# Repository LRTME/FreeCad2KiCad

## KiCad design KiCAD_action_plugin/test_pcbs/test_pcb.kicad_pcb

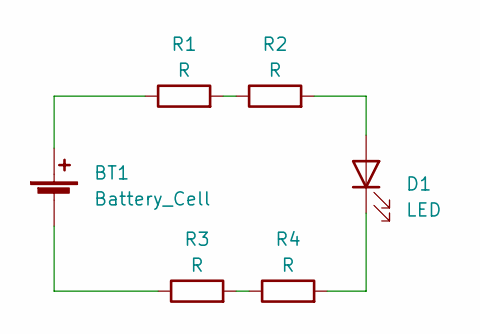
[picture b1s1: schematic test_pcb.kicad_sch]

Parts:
BT1: Battery_Cell; PinHeader_1x02_P1.00mm_Vertical
D1: LED; LED_D5.0mm
R1, R2: R; R_Axial_DIN0204_L3.6mm_D1.6mm_P5.08mm_Horizontal
R3, R4: R; R_1812_4532Metric_Pad1.30x3.40mm_HandSolder

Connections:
unnamed: BT1.1 (+), R1.1
unnamed: BT1.2 (-), R3.1
unnamed: D1.2 (A), R2.2
unnamed: D1.1 (K), R4.2
unnamed: R1.2, R2.1
unnamed: R3.2, R4.1

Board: 2 copper layers, 6 parts (2 on the bottom side), 6 nets, no tracks yet.

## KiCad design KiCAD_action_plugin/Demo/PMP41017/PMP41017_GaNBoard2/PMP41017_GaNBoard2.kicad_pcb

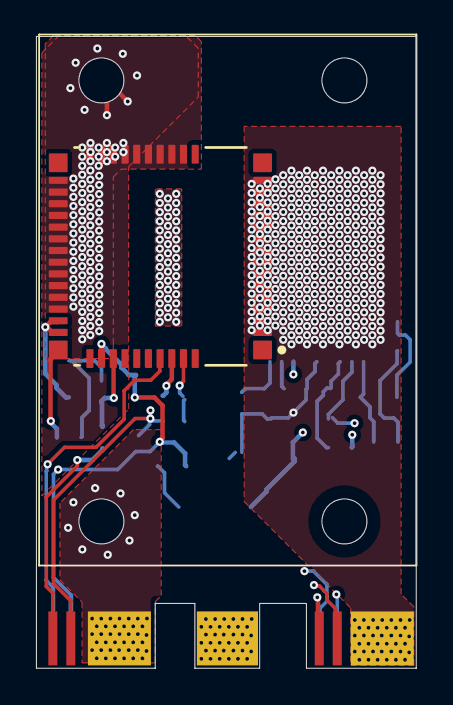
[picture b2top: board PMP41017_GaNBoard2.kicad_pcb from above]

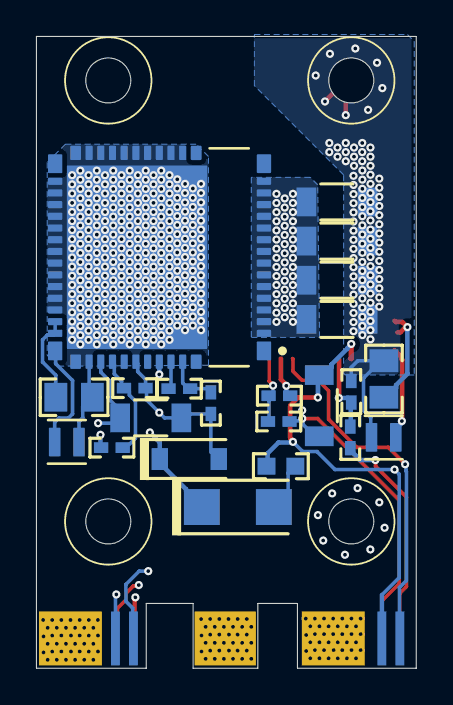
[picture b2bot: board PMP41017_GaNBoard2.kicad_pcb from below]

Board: 4 copper layers, 21.1 x 35.1 mm, 28 parts (27 on the bottom side), 20 nets.

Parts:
C156, C161: C1206C106K3RACTU; 1206_190
C157, C162: CL05B224KO5NNNC; 0402
C158, C163: GRM219R61E225KA12D; 0805_HV
C160, C173: C1005C0G1H220J050BA; 0402
C164, C165, C166, C167: C1206C223KDRACTU; 1206_190
D7: US1M-13-F; SMA
D8: BZT52C16-7-F; SOD-123
J9: Edge Finger; EC_GAN_DC_HBLLC
L7, L8: SDEM20161T-4R7MS; FP-SDEM20161T-4R7MS_SMD2-MFG
R103: MCT06030C2008FP500; 0603
R104, R107: MCR01MZPJ000; 0402
R106, R109: CRCW0402300RJNED; 0402
TH5, TH6, TH7, TH8: M2.5 SCREW; TP_H045P075
U18: LMG3425R030RQZT; RQZ0054A-MFG-NV
U19: LMG3522R030Q; RQS0052A-MFG

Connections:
5V_H: C157.1, R104.2, U18.53
5V_L: C162.2, R107.2, U19.51
HVBUS: C164.1, C165.1, C166.1, C167.1, J9.HV, U18.2, U18.3, U18.4, U18.5, U18.6, U18.7, U18.8, U18.9, U18.10, U18.11, U18.12, U18.13, U18.14, U18.15
INH: J9.6, R106.1
INL: J9.2, R109.1
ISO_12V_H: C156.1, D7.1, D8.1, J9.7, U18.46
ISO_12V_L: C161.2, J9.3, R103.2, U19.44
NetC160_2: C160.2, R106.2, U18.47
NetC173_2: C173.2, R109.2, U19.45
NetD7_2: D7.2, R103.1
NetL7_2: L7.2, U18.43
NetL8_2: L8.2, U19.42
NetR107_1: R107.1, U19.50
PGND: C161.1, C162.1, C163.2, C164.2, C165.2, C166.2, C167.2, C173.1, J9.4, J9.PG, L8.1, U19.18, U19.19, U19.20, U19.21, U19.22, U19.23, U19.24, U19.25, U19.26, U19.28, U19.29, U19.30, U19.31, U19.32, U19.33, U19.34, U19.35, U19.36, U19.37, U19.38, U19.39
RDRV_H_1: R104.1, U18.52
SW: C156.2, C157.2, C158.2, C160.1, D8.2, J9.8, J9.SW, L7.1, U18.18, U18.19, U18.20, U18.21, U18.22, U18.23, U18.24, U18.25, U18.26, U18.27, U18.29, U18.30, U18.31, U18.32, U18.33, U18.34, U18.35, U18.36, U18.37, U18.38, U18.39, U18.40, U18.44, U18.45, U18.49, U18.55, U19.2, U19.3, U19.4, U19.5, U19.6, U19.7, U19.8, U19.9, U19.10, U19.11, U19.12, U19.13, U19.14, U19.15
TEMP_H_1: J9.5, U18.51
TEMP_L_1: J9.1, U19.49
VNEG_H_1: C158.1, U18.41, U18.42
VNEG_L_1: C163.1, U19.40, U19.41

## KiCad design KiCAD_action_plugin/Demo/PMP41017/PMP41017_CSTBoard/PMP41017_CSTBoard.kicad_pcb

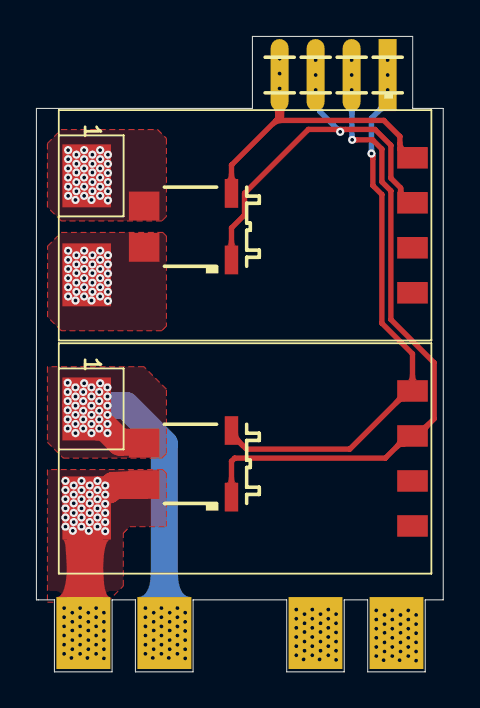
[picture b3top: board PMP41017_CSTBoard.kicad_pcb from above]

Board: 4 copper layers, 22.6 x 35.3 mm, 6 parts (0 on the bottom side), 8 nets.

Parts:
CST1, CST2: PAS6322.050NLT; Pulse_PAS6322
CST1R, CST2R: CST7030-050LC; Coilcraft_CST7030
EC5: Edge Finger; EC_CST
EC6: PTT-104-01-L-S; Samtec_PTT-104-01-x-S

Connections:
CT1p_in: CST1.2, CST1R.4, EC5.4
CT1p_out: CST1.1, CST1R.3, EC5.3
CT1s_neg: CST1.5, CST1R.1, EC6.2
CT1s_pos: CST1.6, CST1R.2, EC6.1
CT2p_in: CST2.1, CST2R.3, EC5.1
CT2p_out: CST2.2, CST2R.4, EC5.2
CT2s_neg: CST2.6, CST2R.2, EC6.4
CT2s_pos: CST2.5, CST2R.1, EC6.3

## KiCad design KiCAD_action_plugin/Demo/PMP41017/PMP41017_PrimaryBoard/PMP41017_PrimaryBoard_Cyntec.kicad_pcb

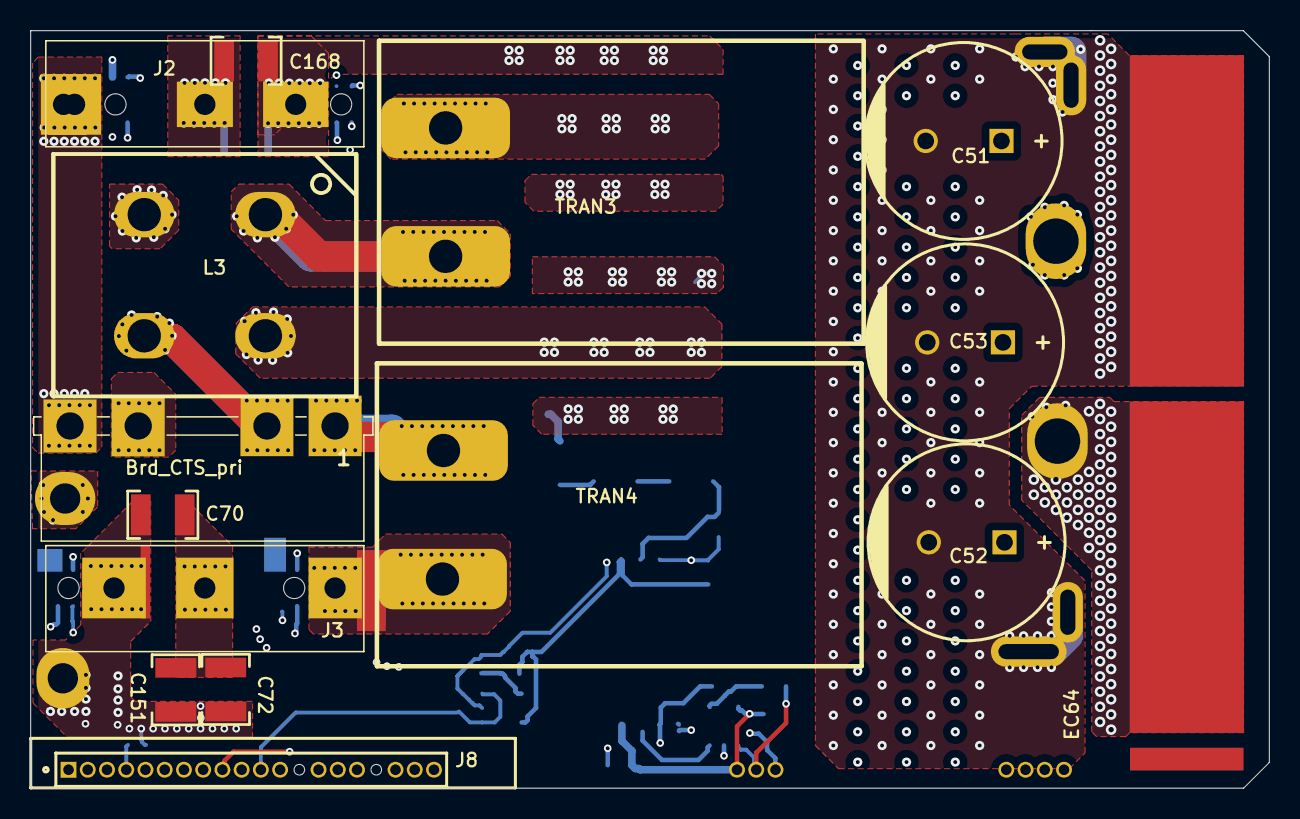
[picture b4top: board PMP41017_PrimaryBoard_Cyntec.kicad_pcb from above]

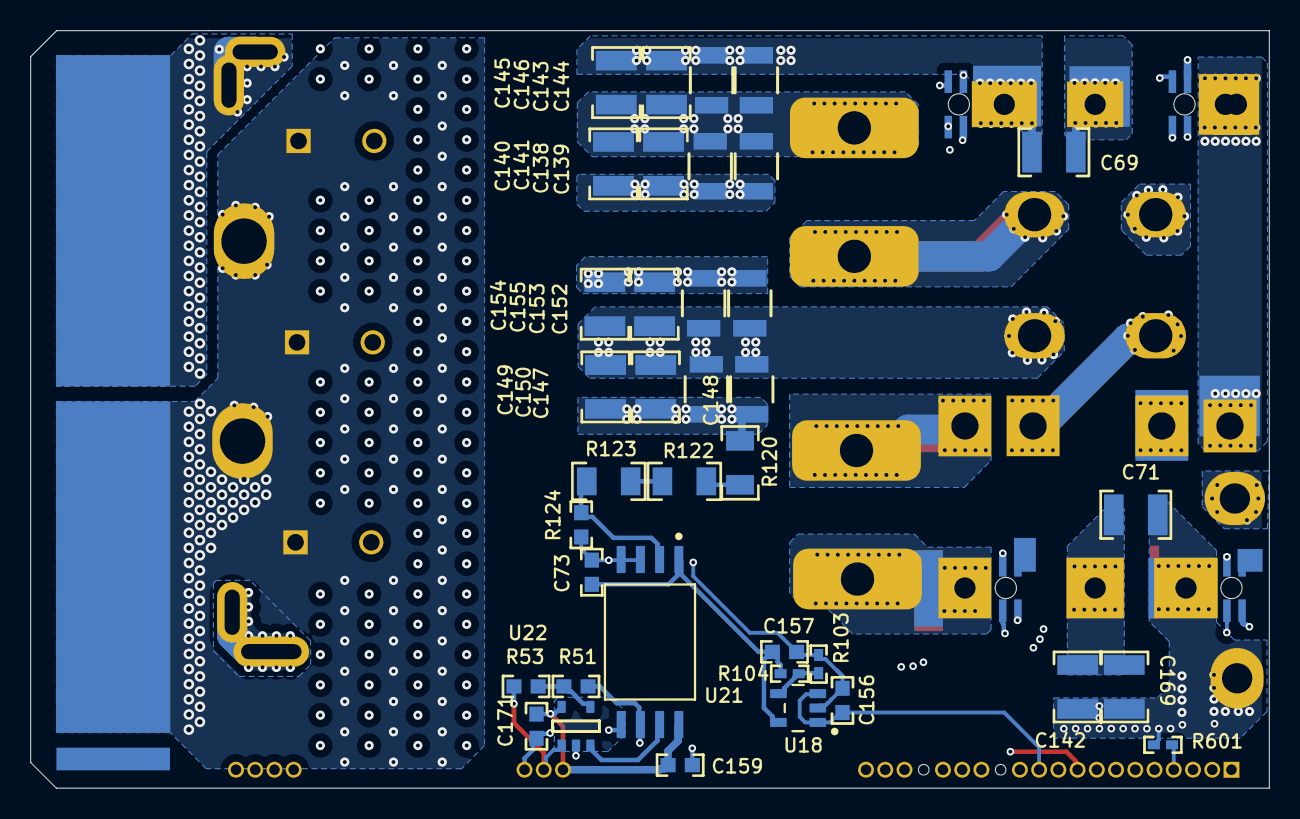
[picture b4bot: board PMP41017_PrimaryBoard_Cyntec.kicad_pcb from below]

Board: 4 copper layers, 81.8 x 50.0 mm, 52 parts (37 on the bottom side), 34 nets.

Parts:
Brd_CTS_pri: CTS daughter board; DB_PMP41017_CST
C51, C52, C53: 860020378023
C69, C70, C71, C72, C142, C151, C168, C169: CGA6L1X7T2J104K160AC; 1210_200
C73, C159, C171: GCM188R71E104KA57D; 0603
C138, C139, C143, C144, C147, C148, C152, C153: C3225C0G2J333J250AA; 1210_280
C140, C145, C149, C154: CGA6N4NP02J223J230AA; 1210_250
C141, C146, C150, C155: CGA6J4C0G2J103J125AA; 1210_150
C156, C157: C1608X7R1E104K080AA; 0603
EC64: EDGE_CONN_PCIe-x4; EC_10035388-102LF
J2, J3: GaN Borad
J8: M52-5002045
L3: PQ2016; CHOKE-PQ2016 - H
R51, R53, R124: RC0603FR-0712KL; 0603
R103, R104, R601: 0402
R120, R122, R123: CRCW12061M00FKEA; 1206
TRAN3, TRAN4: PQ32; PQ3220-1500-400V12V_pri
U18: TPS7A2401DBVR; DBV0005A-MFG
U21: AMC1311BQDWVRQ1; DWV0008A-MFG
U22: TS321IDBVR; DBV0005A_L

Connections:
3V3p_1: C73.1, C157.1, R104.2, U18.5, U21.1
12VL: C156.1, J2.3, J3.3, J8.11, U18.1, U18.3
12Vout: C51.1, C52.1, C53.1, EC64.A10, EC64.A11, EC64.A12, EC64.A13, EC64.A14, EC64.A15, EC64.A16, EC64.A17, EC64.A18, EC64.B10, EC64.B11, EC64.B12, EC64.B13, EC64.B14, EC64.B15, EC64.B16, EC64.B17, EC64.B18
CT1_N: Brd_CTS_pri.3, L3.2
CT1_P: Brd_CTS_pri.4, J2.SW
CT2_N: Brd_CTS_pri.2, L3.3
CT2_P: Brd_CTS_pri.1, TRAN4.2
GAN1_SW1_D: J2.8, J8.18
GaN1_12V_H: J2.7, J8.20
GaN1_INH: J2.6, J8.19
GaN1_INL: J2.2, J8.12
GaN2_12V_H: J3.7, J8.16
GaN2_INH: J3.6, J8.15
GaN2_INL: J3.2, J8.10
GaN2_SW: J3.SW, TRAN4.1
GaN2_SW_D: J3.8, J8.14
HVBUS: C69.1, C70.1, C71.1, C72.1, C138.1, C139.1, C140.1, C141.1, C142.1, C147.1, C148.1, C149.1, C150.1, C151.1, C168.1, C169.1, J2.HV, J3.HV, J8.1, R120.2
NetC147_2: C147.2, C148.2, C149.2, C150.2, C152.1, C153.1, C154.1, C155.1, L3.4
NetR51_1: R51.1, R53.2, U22.4
NetR51_2: R51.2, U21.6
NetR103_2: R103.2, R104.1, U18.4
NetR120_1: R120.1, R122.2
NetR122_1: R122.1, R123.2
NetR123_1: R123.1, R124.2, U21.2
NetU21_7: U21.7, U22.3
PB_3V3-s: C159.1, C171.1, U21.8, U22.5
PB_AGND-s: C159.2, C171.2, U21.5, U22.2
PB_DGNDp: J8.4, R601.2
PB_GND_D: J2.4, J3.4, J8.9
PB_PGND: C69.2, C70.2, C71.2, C72.2, C73.2, C142.2, C143.2, C144.2, C145.2, C146.2, C151.2, C152.2, C153.2, C154.2, C155.2, C156.2, C157.2, C168.2, C169.2, J2.PG, J3.PG, R103.1, R124.1, R601.1, U18.2, U21.3, U21.4
TR1_HV_N: C138.2, C139.2, C140.2, C141.2, C143.1, C144.1, C145.1, C146.1, TRAN3.2
TR1_HV_P: L3.1, TRAN3.1
V0-out: C51.2, C52.2, C53.2, EC64.A1, EC64.A2, EC64.A3, EC64.A4, EC64.A5, EC64.A6, EC64.A7, EC64.A8, EC64.A9, EC64.B1, EC64.B2, EC64.B3, EC64.B4, EC64.B5, EC64.B6, EC64.B7, EC64.B8, EC64.B9
VPRI: R53.1, U22.1

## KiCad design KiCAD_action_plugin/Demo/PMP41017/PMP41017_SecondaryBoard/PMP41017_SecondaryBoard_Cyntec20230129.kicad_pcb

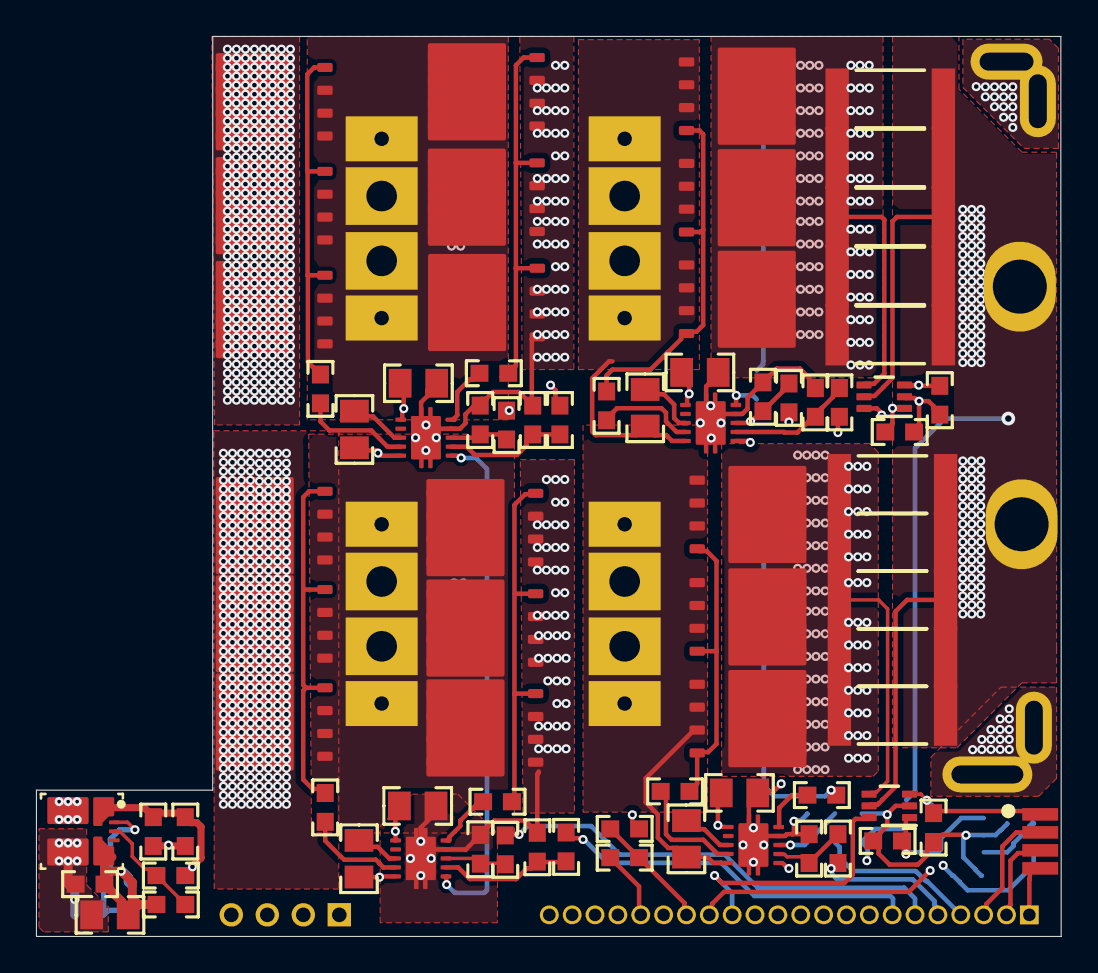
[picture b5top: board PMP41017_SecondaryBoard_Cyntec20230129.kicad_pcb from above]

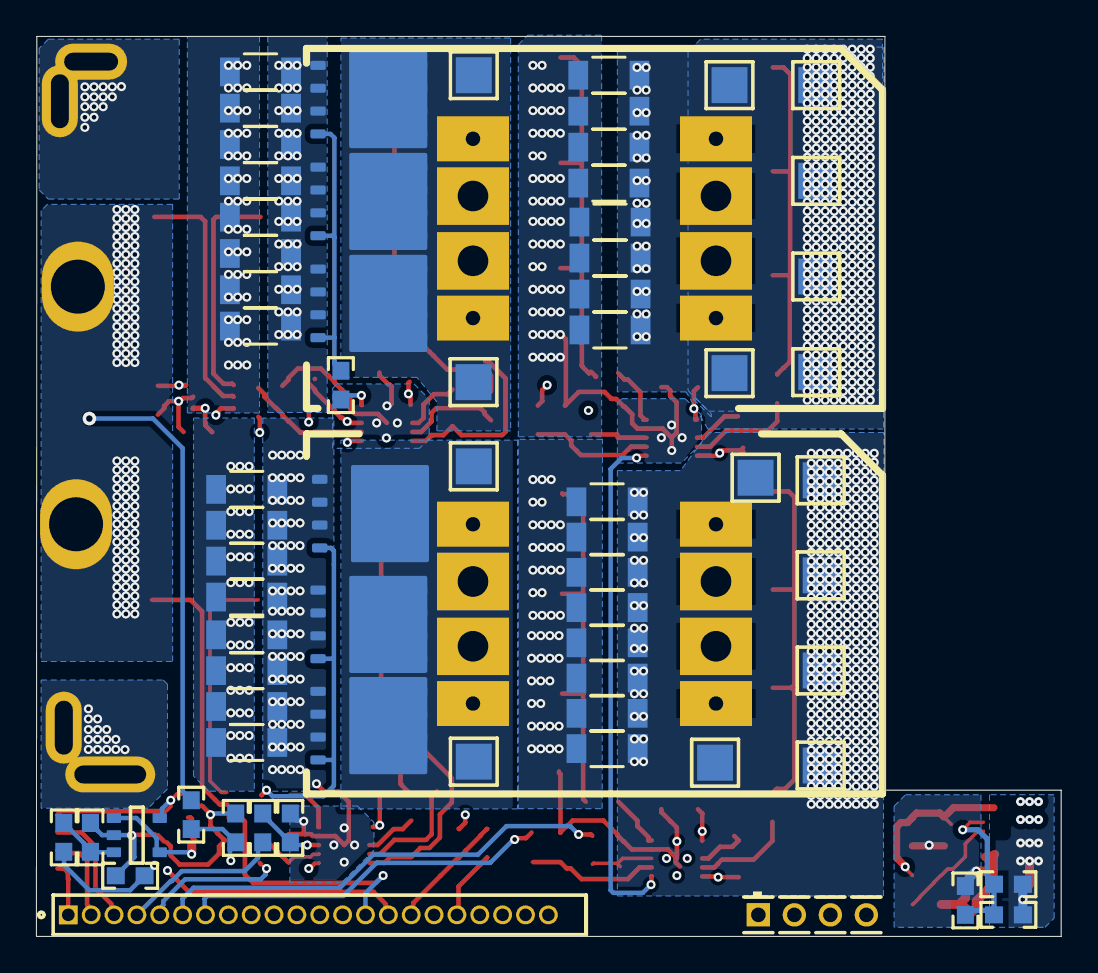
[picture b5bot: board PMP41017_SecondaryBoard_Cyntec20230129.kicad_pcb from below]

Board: 6 copper layers, 56.9 x 50.0 mm, 147 parts (70 on the bottom side), 62 nets.

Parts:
C1, C6: C0603C104K5RACTU; 0603
C2: GRM21BC81C226ME44L; 0805_HV
C4, C7, C8, C9, C10, C11, C12, C13, C14, C15, C16, C25, C26, C27, C28, C29, C30, C31, C32, C33, C34, C35, C36, C37, C38, C39, C40, C101, C102, C103, C106, C137: GMK316AB7106KL-TR; 1206_190
C5: C1608X5R1E106M080AC; 0603
C17, C18, C19, C20, C41, C42, C43, C44: C2012X7R1V475K125AC; 0805_HV
C21, C22, C23, C24, C45, C46, C47, C48: CGA3E2C0G1H101J080AA; 0603
C49, C50, C55, C56, C60: C1608X7R1E104K080AA; 0603
C51: GRM1885C2A330JA01D; 0603
C54: C0603C471K5RACTU; 0603
CSTs: PTT-104-01-L-S; Samtec_PTT-104-01-x-S
J7: M52-5002345; M52-5012345
MP1, MP2, MP3, MP4, MP5, MP6, MP7, MP8, MP9, MP10, MP11, MP12, MP13, MP14, MP15, MP16: 2mmx2mm copper; Copper 2x2
P1: EDGE_CONN_503480-0400; JAE_EDGE_CONN_503480-0400
Q1, Q2, Q4, Q5, Q7, Q8, Q9, Q10, Q12, Q13, Q15, Q16, Q17, Q18, Q21, Q22, Q23, Q24, Q25, Q26, Q27, Q30, Q31, Q32: CSD17573Q5B; DNK0008A
R1: CRCW060330K0JNEA; 0603
R2: CRCW060320K0JNEA; 0603
R3: RC0603FR-07220KL; 0603
R5: 15K 0603; 0603
R23, R118: RC0603FR-075K1L; 0603
R26, R29, R56, R89, R92, R94, R97, R105, R108, R117: CSNL2512FTL500; 2512
R31, R34, R36, R39, R58, R59: ERJ-3RQF2R2V; 0603
R42, R44, R47, R49, R67, R86, R87, R88, R98, R119: RC0603FR-07100RL; 0603
R62, R63: ERJ-3RQF1R0V; 0603
R96: RC0603FR-0720KL; 0603
TRAN1, TRAN2: PQ32; 86H-22072
U1: TPSM863252RDX; RDX0007A-MFG
U2, U3, U4, U10: UCC27282DRCR; DRC0010J
U5, U6: INA210BIDCKR; DCK0006A_N
U20: TS321IDBVR; DBV0005A_L

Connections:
12Vo_A: C4.1, C7.1, C8.1, C9.1, C10.1, C11.1, C12.1, C13.1, C14.1, C15.1, C16.1, C101.1, C102.1, C103.1, C106.1, C137.1, MP1.1, MP2.1, MP3.1, MP4.1, MP5.1, MP6.1, Q1.5, Q1.6, Q1.7, Q1.8, Q1.9, Q2.5, Q2.6, Q2.7, Q2.8, Q2.9, Q4.5, Q4.6, Q4.7, Q4.8, Q4.9, Q5.5, Q5.6, Q5.7, Q5.8, Q5.9, Q7.5, Q7.6, Q7.7, Q7.8, Q7.9, Q8.5, Q8.6, Q8.7, Q8.8, Q8.9, R26.2, R29.2, R89.2, R92.2, R108.2, U5.4
12Vo_B: C25.1, C26.1, C27.1, C28.1, C29.1, C30.1, C31.1, C32.1, C33.1, C34.1, C35.1, C36.1, C37.1, C38.1, C39.1, C40.1, MP7.1, MP8.1, MP9.1, MP10.1, MP11.1, MP12.1, Q17.5, Q17.6, Q17.7, Q17.8, Q17.9, Q18.5, Q18.6, Q18.7, Q18.8, Q18.9, Q21.5, Q21.6, Q21.7, Q21.8, Q21.9, Q22.5, Q22.6, Q22.7, Q22.8, Q22.9, Q23.5, Q23.6, Q23.7, Q23.8, Q23.9, Q24.5, Q24.6, Q24.7, Q24.8, Q24.9, R56.2, R94.2, R97.2, R105.2, R117.2, U6.4
12Vout: R26.1, R29.1, R56.1, R89.1, R92.1, R94.1, R96.1, R97.1, R105.1, R108.1, R117.1, U5.5, U6.5
12Vs: C5.1, C6.1, J7.13, R1.1, U1.1
LV_SW1A: C19.2, Q1.1, Q1.2, Q1.3, Q5.1, Q5.2, Q5.3, Q7.1, Q7.2, Q7.3, Q9.5, Q9.6, Q9.7, Q9.8, Q9.9, Q13.5, Q13.6, Q13.7, Q13.8, Q13.9, Q15.5, Q15.6, Q15.7, Q15.8, Q15.9, TRAN1.1, TRAN1.1ab, TRAN1.1cd, TRAN1.1e, U10.5
LV_SW1B: C20.2, MP13.1, MP15.1, Q2.1, Q2.2, Q2.3, Q4.1, Q4.2, Q4.3, Q8.1, Q8.2, Q8.3, Q10.5, Q10.6, Q10.7, Q10.8, Q10.9, Q12.5, Q12.6, Q12.7, Q12.8, Q12.9, Q16.5, Q16.6, Q16.7, Q16.8, Q16.9, TRAN1.2, TRAN1.2ab, TRAN1.2cd, TRAN1.2e, U2.5
LV_SW2A: C43.2, Q17.1, Q17.2, Q17.3, Q21.1, Q21.2, Q21.3, Q23.1, Q23.2, Q23.3, Q25.5, Q25.6, Q25.7, Q25.8, Q25.9, Q27.5, Q27.6, Q27.7, Q27.8, Q27.9, Q31.5, Q31.6, Q31.7, Q31.8, Q31.9, TRAN2.1, TRAN2.1ab, TRAN2.1cd, TRAN2.1e, U3.5
LV_SW2B: C44.2, MP14.1, MP16.1, Q18.1, Q18.2, Q18.3, Q22.1, Q22.2, Q22.3, Q24.1, Q24.2, Q24.3, Q26.5, Q26.6, Q26.7, Q26.8, Q26.9, Q30.5, Q30.6, Q30.7, Q30.8, Q30.9, Q32.5, Q32.6, Q32.7, Q32.8, Q32.9, TRAN2.2, TRAN2.2ab, TRAN2.2cd, TRAN2.2e, U4.5
NetC19_1: C19.1, U10.3
NetC20_1: C20.1, U2.3
NetC21_2: C21.2, R47.2, U10.8
NetC22_2: C22.2, R42.2, U10.7
NetC23_2: C23.2, R49.2, U2.8
NetC24_2: C24.2, R44.2, U2.7
NetC43_1: C43.1, U3.3
NetC44_1: C44.1, U4.3
NetC45_2: C45.2, R87.2, U3.8
NetC46_2: C46.2, R67.2, U3.7
NetC47_2: C47.2, R88.2, U4.8
NetC48_2: C48.2, R86.2, U4.7
NetC51_2: C51.2, R3.1, R5.2, U1.7
NetQ1_4: Q1.4, Q5.4, Q7.4, R31.2
NetQ2_4: Q2.4, Q4.4, Q8.4, R34.2
NetQ9_4: Q9.4, Q13.4, Q15.4, R36.2
NetQ10_4: Q10.4, Q12.4, Q16.4, R39.2
NetQ17_4: Q17.4, Q21.4, Q23.4, R58.2
NetQ18_4: Q18.4, Q22.4, Q24.4, R59.2
NetQ25_4: Q25.4, Q27.4, Q31.4, R62.2
NetQ26_4: Q26.4, Q30.4, Q32.4, R63.2
NetR1_2: R1.2, R2.1, U1.6
NetR23_2: R23.2, R96.2, R98.1
NetR118_1: R118.1, R119.2, U20.3
PB_3V3-s: C49.1, C50.1, C60.2, J7.12, P1.1, R118.2, U5.3, U6.3, U20.5
PB_AGND-s: C49.2, C50.2, C54.2, C55.1, C56.1, C60.1, J7.18, R23.1, R119.1, U5.2, U6.2, U20.2
PB_CT1+: CSTs.1, J7.22
PB_CT1-: CSTs.2, J7.21
PB_CT2+: CSTs.3, J7.20
PB_CT2-: CSTs.4, J7.19
PB_ISEC1: J7.15, U5.6
PB_ISEC2: J7.14, U6.6
PB_URAT2_RX: J7.3, P1.2
PB_URAT2_TX: J7.2, P1.3
PB_VSEC: C54.1, J7.16, R98.2
SR1_AH: J7.11, R42.1
SR1_AL: J7.10, R47.1
SR1_BH: J7.9, R44.1
SR1_BL: J7.8, R49.1
SR2_AH: J7.7, R67.1
SR2_AL: J7.6, R87.1
SR2_BH: J7.5, R86.1
SR2_BL: J7.4, R88.1
V0-out: C1.2, C2.2, C4.2, C5.2, C6.2, C7.2, C8.2, C9.2, C10.2, C11.2, C12.2, C13.2, C14.2, C15.2, C16.2, C17.2, C18.2, C21.1, C22.1, C23.1, C24.1, C25.2, C26.2, C27.2, C28.2, C29.2, C30.2, C31.2, C32.2, C33.2, C34.2, C35.2, C36.2, C37.2, C38.2, C39.2, C40.2, C41.2, C42.2, C45.1, C46.1, C47.1, C48.1, C101.2, C102.2, C103.2, C106.2, C137.2, J7.1, P1.4, Q9.1, Q9.2, Q9.3, Q10.1, Q10.2, Q10.3, Q12.1, Q12.2, Q12.3, Q13.1, Q13.2, Q13.3, Q15.1, Q15.2, Q15.3, Q16.1, Q16.2, Q16.3, Q25.1, Q25.2, Q25.3, Q26.1, Q26.2, Q26.3, Q27.1, Q27.2, Q27.3, Q30.1, Q30.2, Q30.3, Q31.1, Q31.2, Q31.3, Q32.1, Q32.2, Q32.3, R2.2, R5.1, U1.4, U2.9, U2.11, U3.9, U3.11, U4.9, U4.11, U10.9, U10.11
VDD: C1.1, C2.1, C17.1, C18.1, C41.1, C42.1, C51.1, R3.2, U1.3, U2.1, U2.6, U3.1, U3.6, U4.1, U4.6, U10.1, U10.6
VG_SR1_AH: R31.1, U10.4
VG_SR1_AL: R36.1, U10.10
VG_SR1_BH: R34.1, U2.4
VG_SR1_BL: R39.1, U2.10
VG_SR2_AH: R58.1, U3.4
VG_SR2_AL: R62.1, U3.10
VG_SR2_BH: R59.1, U4.4
VG_SR2_BL: R63.1, U4.10
Vref: C55.2, C56.2, U5.1, U6.1, U20.1, U20.4

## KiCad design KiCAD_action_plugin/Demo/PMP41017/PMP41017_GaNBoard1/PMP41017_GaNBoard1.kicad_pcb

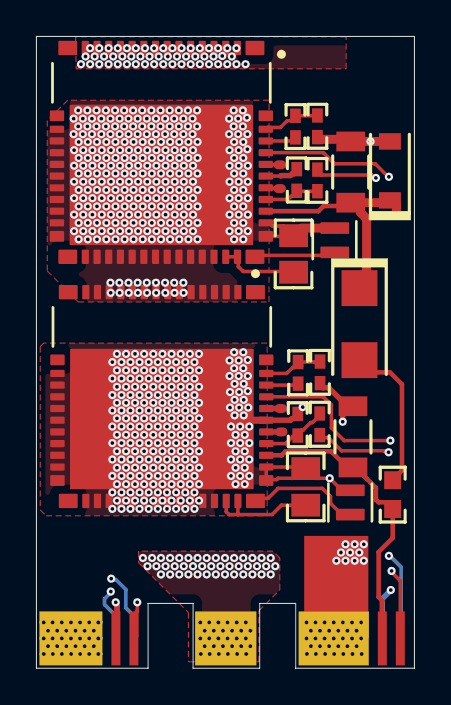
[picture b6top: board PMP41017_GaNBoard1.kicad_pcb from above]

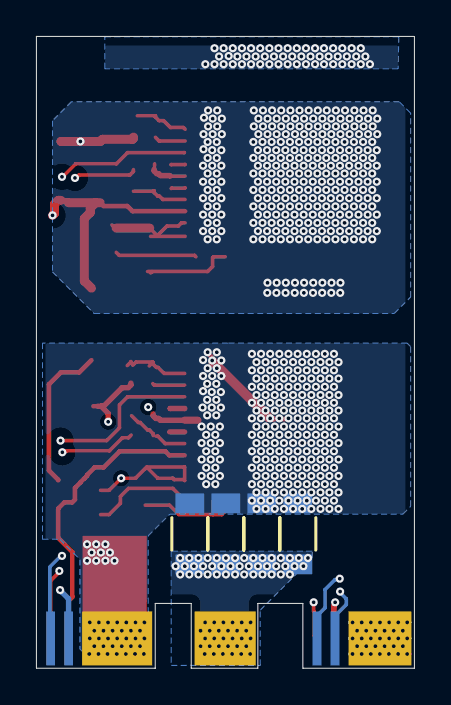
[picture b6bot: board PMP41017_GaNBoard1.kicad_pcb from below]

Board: 4 copper layers, 21.0 x 35.1 mm, 24 parts (4 on the bottom side), 20 nets.

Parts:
C57, C62: C1206C106K3RACTU; 1206_190
C58, C63: CL05B224KO5NNNC; 0402
C59, C64: GRM219R61E225KA12D; 0805_HV
C61, C170: C1005C0G1H220J050BA; 0402
C65, C66, C67, C68: C1206C223KDRACTU; 1206_190
D1: US1M-13-F; SMA
D2: BZT52C16-7-F; SOD-123
J1: Edge Finger; EC_GAN_DC_HBLLC
L1, L4: SDEM20161T-4R7MS; FP-SDEM20161T-4R7MS_SMD2-MFG
R24: MCT06030C2008FP500; 0603
R25, R28: MCR01MZPJ000; 0402
R27, R110: CRCW0402300RJNED; 0402
U7, U8: LMG3425R030RQZT; RQZ0054A-MFG-NV

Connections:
5V_H: C58.1, R25.2, U7.53
5V_L: C63.1, R28.2, U8.53
HVBUS: C65.1, C66.1, C67.1, C68.1, J1.HV, U7.2, U7.3, U7.4, U7.5, U7.6, U7.7, U7.8, U7.9, U7.10, U7.11, U7.12, U7.13, U7.14, U7.15
INH: J1.6, R27.1
INL: J1.2, R110.1
ISO_12V_H: C57.1, D1.1, D2.1, J1.7, U7.46
ISO_12V_L: C62.2, J1.3, R24.2, U8.46
NetC61_2: C61.2, R27.2, U7.47
NetC170_2: C170.2, R110.2, U8.47
NetD1_2: D1.2, R24.1
NetL1_2: L1.2, U7.43
NetL4_2: L4.2, U8.43
NetR28_1: R28.1, U8.52
PGND: C62.1, C63.2, C64.2, C65.2, C66.2, C67.2, C68.2, C170.1, J1.4, J1.PG, L4.1, U8.18, U8.19, U8.20, U8.21, U8.22, U8.23, U8.24, U8.25, U8.26, U8.27, U8.29, U8.30, U8.31, U8.32, U8.33, U8.34, U8.35, U8.36, U8.37, U8.38, U8.39, U8.40, U8.44, U8.45, U8.49, U8.55
RDRV_H: R25.1, U7.52
SW: C57.2, C58.2, C59.2, C61.1, D2.2, J1.8, J1.SW, L1.1, U7.18, U7.19, U7.20, U7.21, U7.22, U7.23, U7.24, U7.25, U7.26, U7.27, U7.29, U7.30, U7.31, U7.32, U7.33, U7.34, U7.35, U7.36, U7.37, U7.38, U7.39, U7.40, U7.44, U7.45, U7.49, U7.55, U8.2, U8.3, U8.4, U8.5, U8.6, U8.7, U8.8, U8.9, U8.10, U8.11, U8.12, U8.13, U8.14, U8.15
TEMP_H: J1.5, U7.51
TEMP_L: J1.1, U8.51
VNEG_H: C59.1, U7.41, U7.42
VNEG_L: C64.1, U8.41, U8.42

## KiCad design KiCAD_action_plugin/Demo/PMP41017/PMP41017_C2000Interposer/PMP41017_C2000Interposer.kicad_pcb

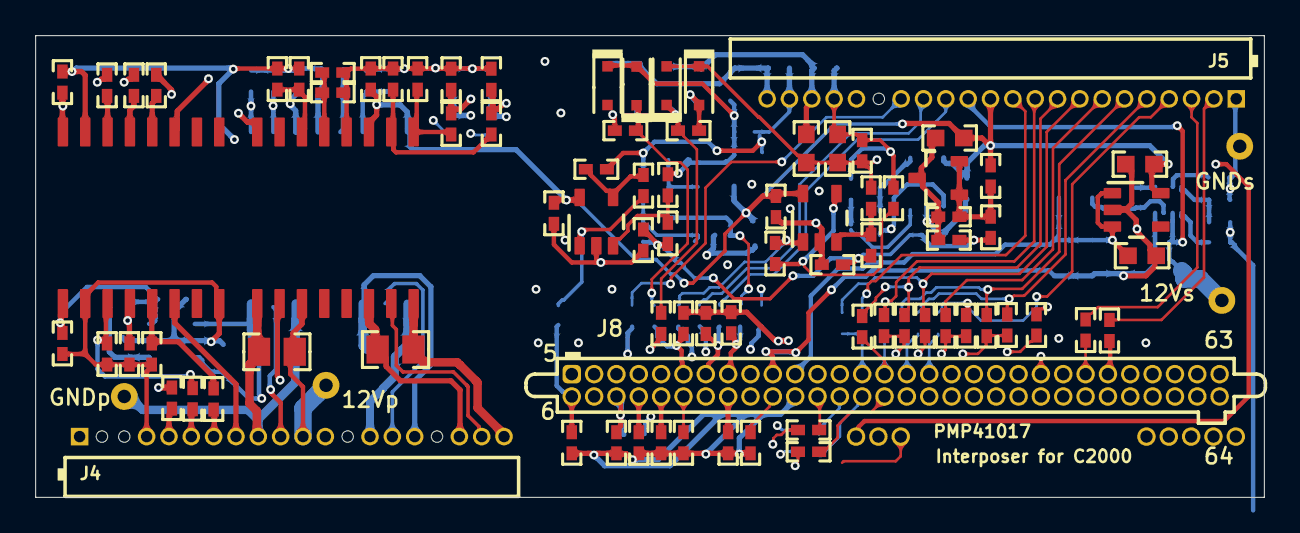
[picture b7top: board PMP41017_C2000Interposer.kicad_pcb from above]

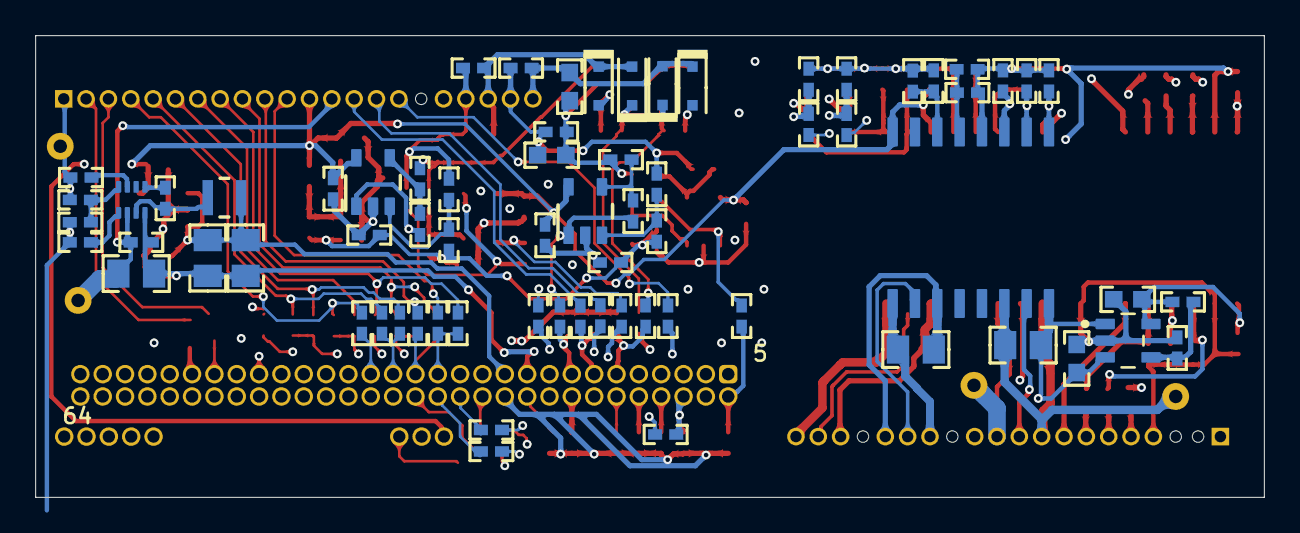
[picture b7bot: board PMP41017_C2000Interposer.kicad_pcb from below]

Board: 4 copper layers, 69.9 x 26.3 mm, 155 parts (70 on the bottom side), 109 nets.

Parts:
C1, C3: GRM155R71E104KE14D; 0402
C2, C5, C6: GRM21BR61E226ME44L; 0805_HV
C74, C75, C76, C78, C82, C84, C85, C86, C87, C89, C111, C112, C113, C114, C120, C121, C122: Cap; 0402
C77, C88, C105, C107: C1608X7R1E104K080AA; 0603
C108: GCM188R71C105MA64D; 0603
C109, C125, C126, C131_VS1, C131_VS2: 0402
C110, C115, C127, C128: 885012105010; 0402
C116, C117, C123, C124: C2012X7R1V475K125AC; 0805_HV
C118, C119: GRM155R71H102KA01D; 0402
C129_VS1, C129_VS2: GRM155R70J105KA12D; 0402
C130_VS1, C130_VS2: DNP; 0603
C133_VS1, C133_VS2, C134_VS1, C134_VS2, C136_VS1, C136_VS2: C1005X7R1H104K050BE; 0402
D3_VS1, D3_VS2, D4_VS1, D4_VS2, D5_VS1, D5_VS2, D6_VS1, D6_VS2: BAS316,115; SOD-323
J4: HTMS-120-01-G-S-RA
J5: HTMS-123-01-G-S-RA
J8: SFM-130-01-S-D; Samtec_SFM-130-01-x-D
L2: 74438323100; VLS252010HBX
R1, R2, R3, R4, R5, R11, R12, R13, R14, R15, R16, R18, R19, R20, R21, R22, R64, R68, R69, R70, R71, R72, R73, R74, R75, R76, R77, R78, R79, R80, R81, R82, R83_VS1, R83_VS2, R85_VS1, R85_VS2, R90_VS1, R90_VS2, R91_VS1, R91_VS2, R95_VS1, R95_VS2, R111_VS1, R111_VS2, R112_VS1, R112_VS2, R114_VS1, R114_VS2, R115_VS1, R115_VS2, R116_VS1, R116_VS2: 0402
R6: 73.2k; 0402
R7, R8, R9, R10, R23, R24, R30, R32, R33, R35, R37, R38, R40, R41, R43, R45, R46, R48, R50, R52, R99, R100, R101, R102: CRCW04020000Z0ED; 0402
R17: 100R; 0402
R84_VS1, R84_VS2: NC; 0603
U1: TPS562211DRLR; DRL0008A
U9: TPS7A2401DBVR; DBV0005A-MFG
U11: TLV71333PDBVT; DBV0005A_N
U12: TLV431BCDBZT; DBZ0003A_N
U13: ISO7741DWR; DW0016B_HV
U14, U15: UCC21540DWR; DW0016B_HV
U16_VS1, U16_VS2, U17_VS1, U17_VS2: OPA365; DBV0005A_N

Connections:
3V3-p_1: C88.1, C110.1, R4.2, U9.5, U13.1
3V3-s: C105.1, C108.1, C115.1, C127.1, C128.1, C133_VS1.2, C133_VS2.2, C136_VS1.2, C136_VS2.2, J5.12, R21.2, U11.5, U13.16, U14.3, U14.8, U15.3, U15.8, U16_VS1.5, U16_VS2.5, U17_VS1.5, U17_VS2.5
5Vcc-s: C5.1, C6.1, C107.1, J8.25, L2.2, R6.2, R19.2, U11.1, U11.3
12Vc-s: C1.2, C2.1, J5.13, U1.2
12Vdp: C77.1, C123.1, C124.1, J4.11, U9.1, U9.3, U14.11, U15.16
12Vp1: C116.1, J4.20, U14.16
12Vp2: C117.1, J4.16, U15.11
AC_OK: J4.5, R75.1
AC_OK_s_1: R45.1, U13.13
AGND-s: C74.1, C75.1, C76.1, C78.1, C82.1, C84.1, C85.1, C86.1, C87.1, C89.1, C108.2, C109.1, C129_VS1.1, C129_VS2.1, C133_VS1.1, C133_VS2.1, C134_VS1.2, C134_VS2.2, C136_VS1.1, C136_VS2.1, D4_VS1.2, D4_VS2.2, D6_VS1.2, D6_VS2.2, J5.18, J8.26, R22.1, R83_VS1.1, R83_VS2.1, U12.3, U16_VS1.2, U16_VS2.2, U17_VS1.2, U17_VS2.2
CT1+: D3_VS1.2, D4_VS1.1, J5.22, R84_VS1.2, R111_VS1.2
CT1-: C130_VS1.1, C131_VS1.2, J5.21, R111_VS1.1, R114_VS1.2, R115_VS1.2
CT2+: D3_VS2.2, D4_VS2.1, J5.20, R84_VS2.2, R111_VS2.2
CT2-: C130_VS2.1, C131_VS2.2, J5.19, R111_VS2.1, R114_VS2.2, R115_VS2.2
CT_I-_VS1: C130_VS1.2, C131_VS1.1, D5_VS1.2, D6_VS1.1, R84_VS1.1, R112_VS1.2, R116_VS1.2
CT_I-_VS2: C130_VS2.2, C131_VS2.1, D5_VS2.2, D6_VS2.1, R84_VS2.1, R112_VS2.2, R116_VS2.2
DGND-p: C123.2, C124.2, J4.9, U14.9, U15.14
DGND-s: C1.1, C2.2, C5.2, C6.2, C105.2, C107.2, C111.2, C112.2, C113.2, C114.2, C115.2, C118.2, C119.2, C125.1, C126.1, C127.2, C128.2, J5.1, J8.23, R3.1, R20.2, R68.2, R69.2, R70.2, R71.2, R79.1, R80.1, R81.1, R82.1, U1.4, U11.2, U13.15, U14.4, U15.4
GNDc-p: C77.2, C88.2, C110.2, C120.1, C121.1, C122.1, J4.4, R5.1, U9.2, U13.2, U13.8
I-reso_VS1: D3_VS1.1, D5_VS1.1, R11.2, R83_VS1.2
I-reso_VS2: D3_VS2.1, D5_VS2.1, R12.2, R83_VS2.2
ISEC1: J5.15, R13.2
ISEC2: J5.14, R14.2
LLC-DRV-1H: J4.19, U14.15
LLC-DRV-1L: J4.12, U14.10
LLC-DRV-2H: J4.15, U15.10
LLC-DRV-2L: J4.10, U15.15
LLC-SW1: C116.2, J4.18, U14.14
LLC-SW2: C117.2, J4.14, U15.9
MCU_A3_1: C89.2, J8.24, R18.1
MCU_A5_1: C74.2, J8.10, R1.1
MCU_A6_1: C75.2, J8.12, R2.1
MCU_A7_1: C82.2, J8.20, R13.1
MCU_A8_1: C76.2, J8.15, R11.1
MCU_A9_1: C84.2, J8.17, R14.1
MCU_A10_1: C78.2, J8.14, R12.1
MCU_B6_1: C85.2, J8.6, R15.1
MCU_B10_1: C87.2, J8.16, R17.1
MCU_B14_1: C86.2, J8.19, R16.1
MCU_GPIO0_1: J8.28, R30.2
MCU_GPIO1_1: J8.30, R32.2
MCU_GPIO2_1: J8.32, R33.2
MCU_GPIO3_1: J8.34, R35.2
MCU_GPIO6_1: J8.31, R7.2, R99.2
MCU_GPIO7_1: J8.33, R23.2, R100.2
MCU_GPIO8_1: J8.36, R8.2, R37.2
MCU_GPIO9_1: J8.38, R38.2
MCU_GPIO10_1: J8.40, R9.2, R40.2
MCU_GPIO11_1: J8.42, R24.2, R41.2
MCU_GPIO12_1: J8.35, R10.2, R101.2
MCU_GPIO13_1: J8.37, R102.2
MCU_GPIO16_1: J8.44, R46.2
MCU_GPIO17_1: J8.46, R48.1
MCU_GPIO22_1: J8.47, R43.2
MCU_GPIO28_1: J8.51, R50.2
MCU_GPIO29_1: J8.53, R52.1
MCU_GPIO33_1: J8.62, R45.2
NetC3_1: C3.1, U1.5
NetC3_2: C3.2, L2.1, U1.3
NetC109_2: C109.2, R21.1, R64.1, U12.1, U12.2
NetC111_1: C111.1, R73.2, U14.1
NetC112_1: C112.1, R76.2, U14.2
NetC113_1: C113.1, R74.2, U15.1
NetC114_1: C114.1, R77.2, U15.2
NetC118_1: C118.1, R79.2, U14.5
NetC119_1: C119.1, R80.2, U15.5
NetC120_2: C120.2, R78.2, U13.5
NetC121_2: C121.2, R75.2, U13.4
NetC122_2: C122.2, R72.2, U13.3
NetC125_2: C125.2, R81.2, U14.6
NetC126_2: C126.2, R82.2, U15.6
NetR3_2: R3.2, U1.7
NetR4_1: R4.1, R5.2, U9.4
NetR6_1: R6.1, R20.1, U1.8
NetR19_1: R19.1, U1.1
NetR85_VS1_2: R85_VS1.2, R112_VS1.1, U16_VS1.3
NetR85_VS2_2: R85_VS2.2, R112_VS2.1, U16_VS2.3
NetR90_VS1_2: R90_VS1.2, R114_VS1.1, U16_VS1.4
NetR90_VS2_2: R90_VS2.2, R114_VS2.1, U16_VS2.4
NetR91_VS1_2: R91_VS1.2, R115_VS1.1, U17_VS1.3
NetR91_VS2_2: R91_VS2.2, R115_VS2.1, U17_VS2.3
NetR95_VS1_2: R95_VS1.2, R116_VS1.1, U17_VS1.4
NetR95_VS2_2: R95_VS2.2, R116_VS2.1, U17_VS2.4
PFC_OK: J4.6, R72.1
PFC_OK_s_1: R43.1, U13.14
PH1_PRI_PWMA_1: R30.1, R69.1, R73.1
PH1_PRI_PWMB_1: R32.1, R68.1, R76.1
PH1_SEC_PWMAH: J5.11, R99.1
PH1_SEC_PWMAL: J5.10, R8.1, R100.1
PH1_SEC_PWMBH: J5.9, R23.1, R37.1
PH1_SEC_PWMBL: J5.8, R7.1, R38.1
PH2_PRI_PWMA_1: R33.1, R70.1, R77.1
PH2_PRI_PWMB_1: R35.1, R71.1, R74.1
PH2_SEC_PWMAH: J5.7, R40.1
PH2_SEC_PWMAL: J5.6, R10.1, R41.1
PH2_SEC_PWMBH: J5.5, R24.1, R101.1
PH2_SEC_PWMBL: J5.4, R9.1, R102.1
RX-PFC: J4.8, U13.6
TX-PFC: J4.7, R78.1
URAT1_RX_s_1: R46.1, U13.12
URAT1_TX_s_1: R48.2, U13.11
URAT2_RX: J5.3, R50.1
URAT2_TX: J5.2, R52.2
VCR-N_VS1: R16.2, R95_VS1.1, U17_VS1.1
VCR-N_VS2: R18.2, R95_VS2.1, U17_VS2.1
VCR-P_VS1: R15.2, R90_VS1.1, U16_VS1.1
VCR-P_VS2: R17.2, R90_VS2.1, U16_VS2.1
VSEC: J5.16, R2.2
Vcm_bias_1: C129_VS1.2, C129_VS2.2, C134_VS1.1, C134_VS2.1, R22.2, R64.2, R85_VS1.1, R85_VS2.1, R91_VS1.1, R91_VS2.1
